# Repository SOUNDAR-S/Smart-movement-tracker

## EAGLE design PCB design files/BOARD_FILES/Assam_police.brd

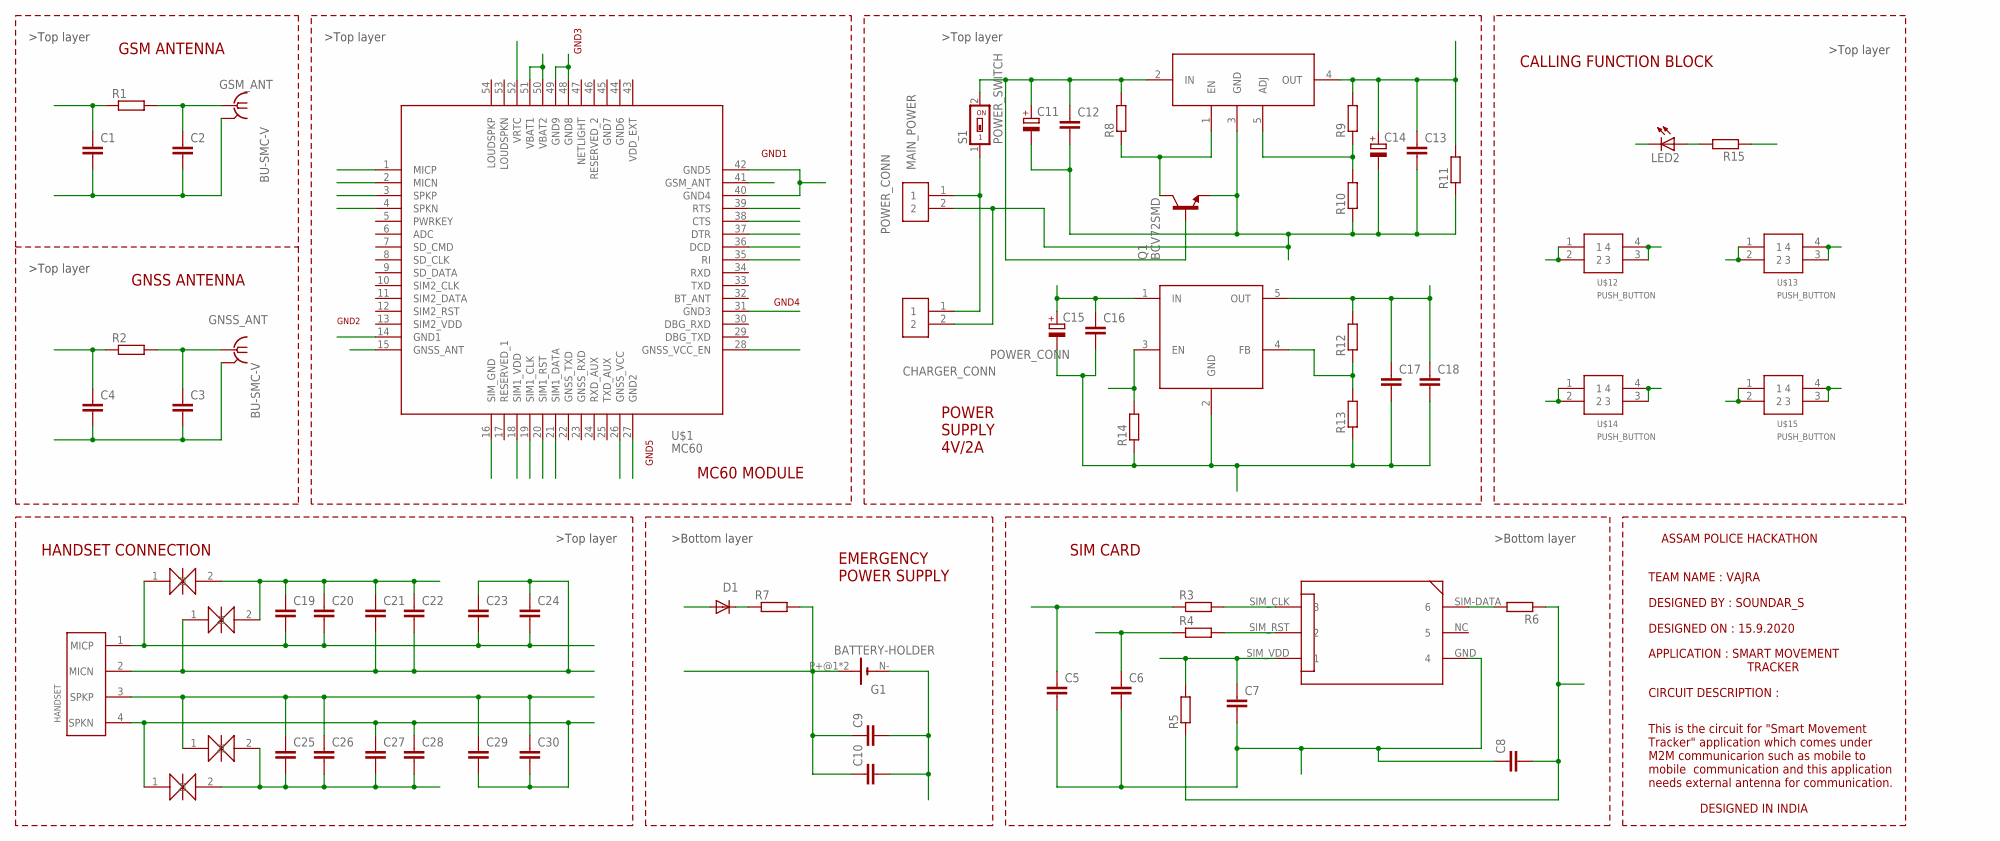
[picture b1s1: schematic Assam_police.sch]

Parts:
C1, C2, C3, C4, C5, C6, C7, C8, C9, C10, C19, C20, C21, C22, C23, C24, C25, C26, C27, C28, C29, C30: C-EUC0603K; C0603K
C11, C14, C15: CPOL-EU140CLH-0810; 140CLH-0810
C12, C13, C16, C17, C18: C-EUC1808; C1808
CHARGER_CONN: POWER_CONN; POWER_PUSH_TYPE
D1: CGRM4001-G; SOD-123_MINI-SMA
G1: BATTERY-HOLDER; CELL_RETAINER_11.6MM
GNSS_ANT: BU-SMC-V
GSM_ANT: BU-SMC-V
LED2: LEDSMT1206; 1206
MAIN_POWER: POWER_CONN; POWER_PUSH_TYPE
Q1: BCV72SMD; SOT23-BEC
R1, R2, R3, R4, R5, R6, R7, R15: R-EU_M3516; M3516
R8, R9, R10, R11, R12, R13, R14: R-EU_MELF0207W; MINI_MELF-0207W
S1: POWER_SWITCH; SMS-001
U$1: MC60
U$2: SIM_MODULE; SIM_6_SMD
U$3: MIC29302; TO-252
U$4: SGM2019
U$5: HANDSET; HANDSET_4
U$6, U$7, U$8, U$9: ESD_DIODE; ESD_PROTECTION_DIODE
U$12, U$13, U$14, U$15: PUSH_BUTTON

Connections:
CALL_CUT0: U$1.37 (DTR), U$13.1, U$13.2
CALL_CUT1: U$1.35 (RI), U$15.1, U$15.2
CALL_MAKING: U$1.36 (DCD), U$14.1, U$14.2
CALL_PICKING: U$1.38 (CTS), U$12.1, U$12.2
GND1: C1.2, C2.2, GSM_ANT.2, GSM_ANT.3 (2), GSM_ANT.4 (2), GSM_ANT.5 (2), LED2.C, U$1.40 (GND4), U$1.42 (GND5)
GND2: C3.2, C4.2, C19.1, C20.1, C21.1, C22.1, C25.2, C26.2, C27.2, C28.2, GNSS_ANT.2, GNSS_ANT.3 (2), GNSS_ANT.4 (2), GNSS_ANT.5 (2), U$1.14 (GND1), U$6.2, U$7.2, U$8.2, U$9.2
GND3: C9.2, C10.2, C11.-, C12.2, C13.2, C14.-, CHARGER_CONN.2, G1.N- (-), MAIN_POWER.2, Q1.E, R10.1, R11.1, U$1.48 (GND8), U$1.49 (GND9), U$3.3 (GND)
GND4: U$1.31 (GND3)
GND5: C15.-, C16.2, C17.2, C18.2, R13.1, R14.1, U$1.27 (GND2), U$4.2 (GND)
GNSS_ANT: C4.1, R2.1, U$1.15 (GNSS_ANT)
GNSS_VCC: C17.1, C18.1, R12.2, U$1.26 (GNSS_VCC), U$4.5 (OUT)
GNSS_VCC_EN: R14.2, U$1.28 (GNSS_VCC_EN), U$4.3 (EN)
GSM_ANT: C1.1, R1.1, U$1.41 (GSM_ANT)
INCOMMING_CALL_INDI: R15.1, U$1.39 (RTS)
MICN: C21.2, C22.2, C23.1, C24.1, U$1.2 (MICN), U$5.2 (MICN), U$7.1
MICP: C19.2, C20.2, C23.2, C24.2, U$1.1 (MICP), U$5.1 (MICP), U$6.1
unnamed: C2.1, GSM_ANT.1, R1.2
unnamed: R3.2, U$2.SIM_CLK (3)
unnamed: R4.2, U$2.SIM_RST (2)
unnamed: C3.1, GNSS_ANT.1, R2.2
unnamed: CHARGER_CONN.1, MAIN_POWER.1, S1.1
unnamed: D1.C, R7.1
unnamed: LED2.A, R15.2
unnamed: R6.2, U$2.SIM-DATA (6)
unnamed: R9.1, R10.2, U$3.5 (ADJ)
unnamed: R12.1, R13.2, U$4.4 (FB)
unnamed: C11.+, C12.1, Q1.B, R8.2, S1.2, U$3.2 (IN)
unnamed: Q1.C, R8.1, U$3.1 (EN)
SIM_CLK: C5.1, R3.1, U$1.19 (SIM1_CLK)
SIM_DATA: C8.2, R5.1, R6.1, U$1.21 (SIM1_DATA)
SIM_GND: C5.2, C6.2, C7.2, C8.1, U$1.16 (SIM_GND), U$2.GND (4)
SIM_RST: C6.1, R4.1, U$1.20 (SIM1_RST)
SIM_VDD: C7.1, R5.2, U$1.18 (SIM1_VDD), U$2.SIM_VDD (1)
SPKN: C27.1, C28.1, C29.2, C30.2, U$1.4 (SPKN), U$5.4 (SPKN), U$9.1
SPKP: C25.1, C26.1, C29.1, C30.1, U$1.3 (SPKP), U$5.3 (SPKP), U$8.1
VBAT: C13.1, C14.+, C15.+, C16.1, D1.A, R9.2, R11.2, U$1.50 (VBAT2), U$1.51 (VBAT1), U$3.4 (OUT), U$4.1 (IN), U$12.3, U$12.4, U$13.3, U$13.4, U$14.3, U$14.4, U$15.3, U$15.4
VRTC: C9.1, C10.1, G1.P+@1 (+), G1.P+@2 (+), R7.2, U$1.52 (VRTC)

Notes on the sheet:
GSM ANTENNA
GNSS ANTENNA
MC60 MODULE
SIM CARD
DESIGNED BY : SOUNDAR_S
DESIGNED ON : 15.9.2020
TEAM NAME : VAJRA
CIRCUIT DESCRIPTION :
This is the circuit for "Smart Movement Tracker" application which comes under M2M communicarion such as mobile to mobile communication and this application needs external antenna for communication.
EMERGENCY POWER SUPPLY
GND1
GND2
POWER SUPPLY 4V/2A
HANDSET CONNECTION
DESIGNED IN INDIA
GND3
GND4
CALLING FUNCTION BLOCK
APPLICATION : SMART MOVEMENT TRACKER
GND5
ASSAM POLICE HACKATHON

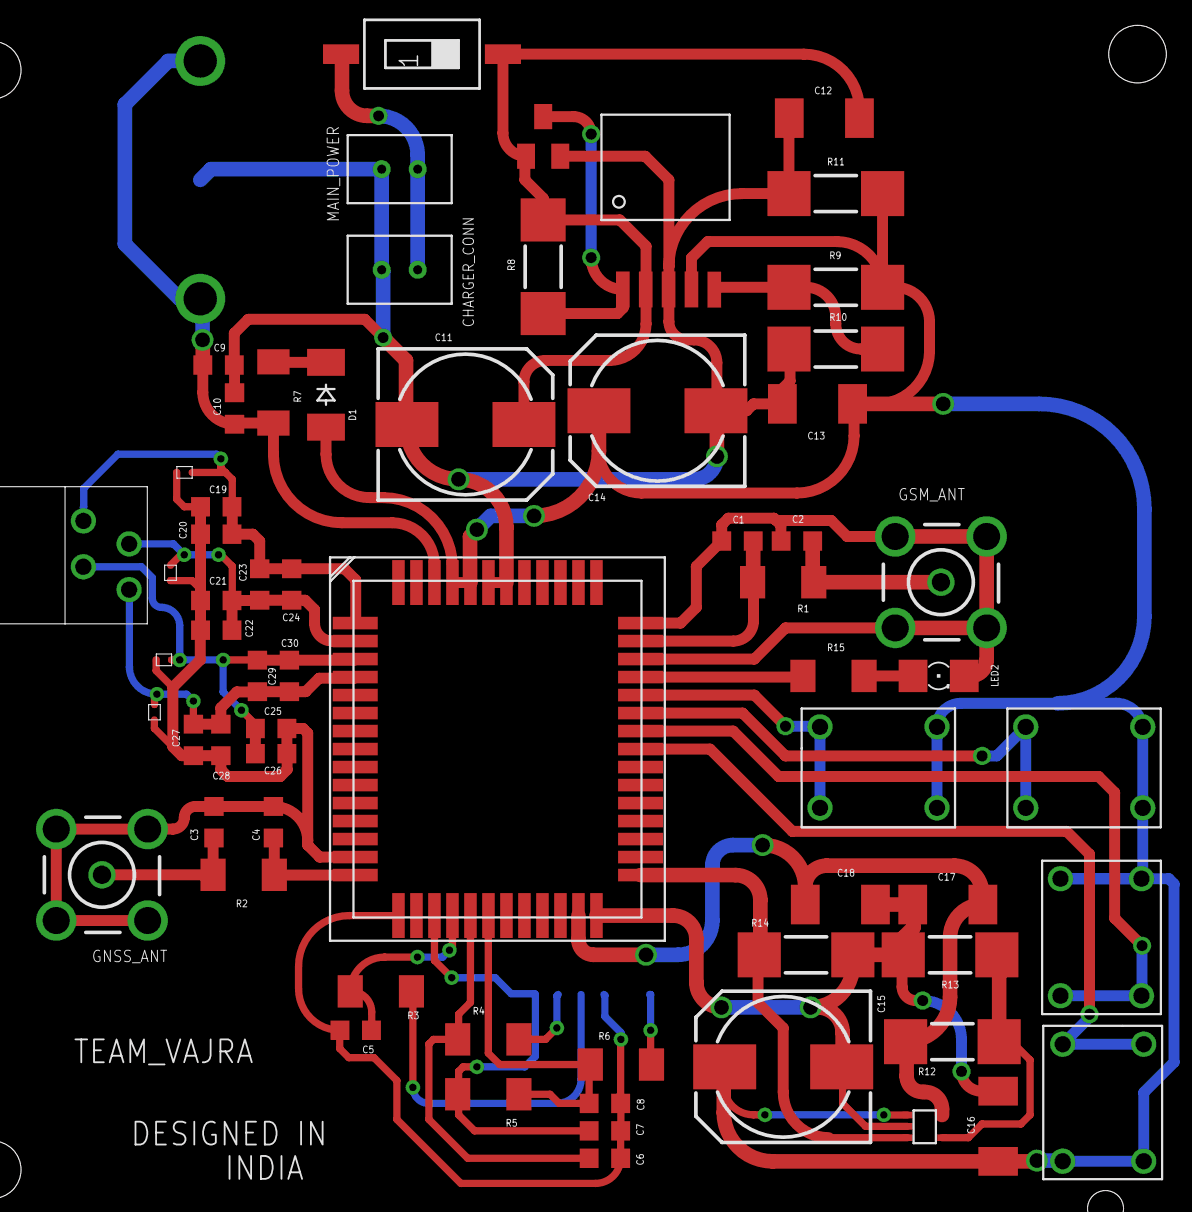
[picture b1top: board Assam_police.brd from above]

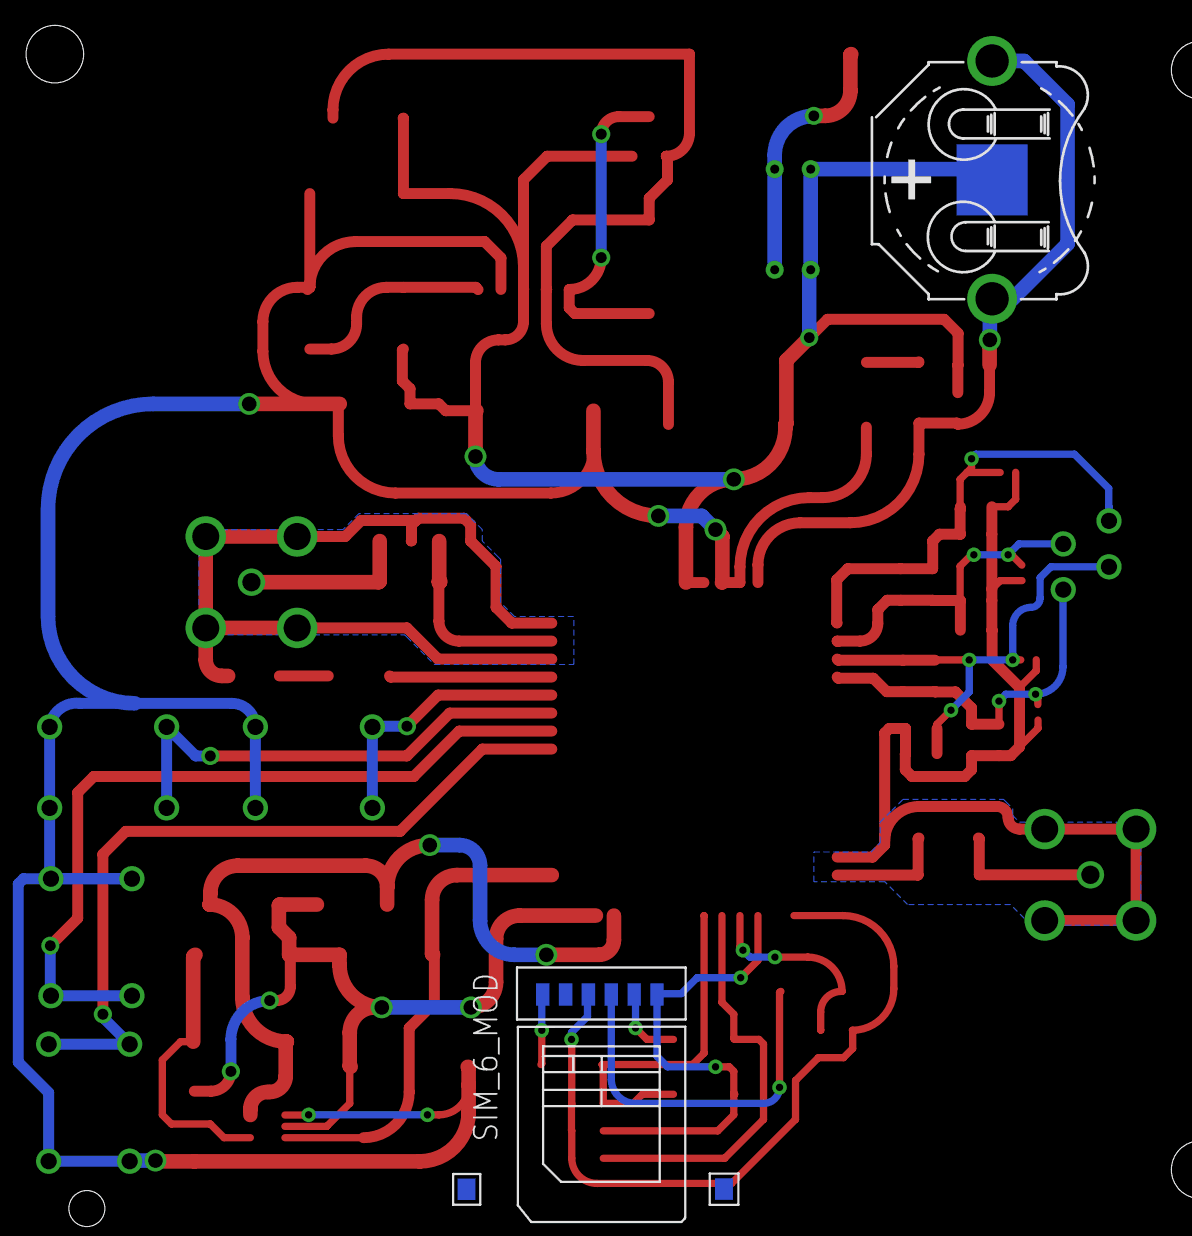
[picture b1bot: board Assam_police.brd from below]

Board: 2 copper layers, 67 parts (2 on the bottom side), 36 nets.

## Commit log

2020-09-28 PCB files
2020-09-28 Demo video
2020-09-28 Images
2020-09-28 Add files via upload
    Presentation
